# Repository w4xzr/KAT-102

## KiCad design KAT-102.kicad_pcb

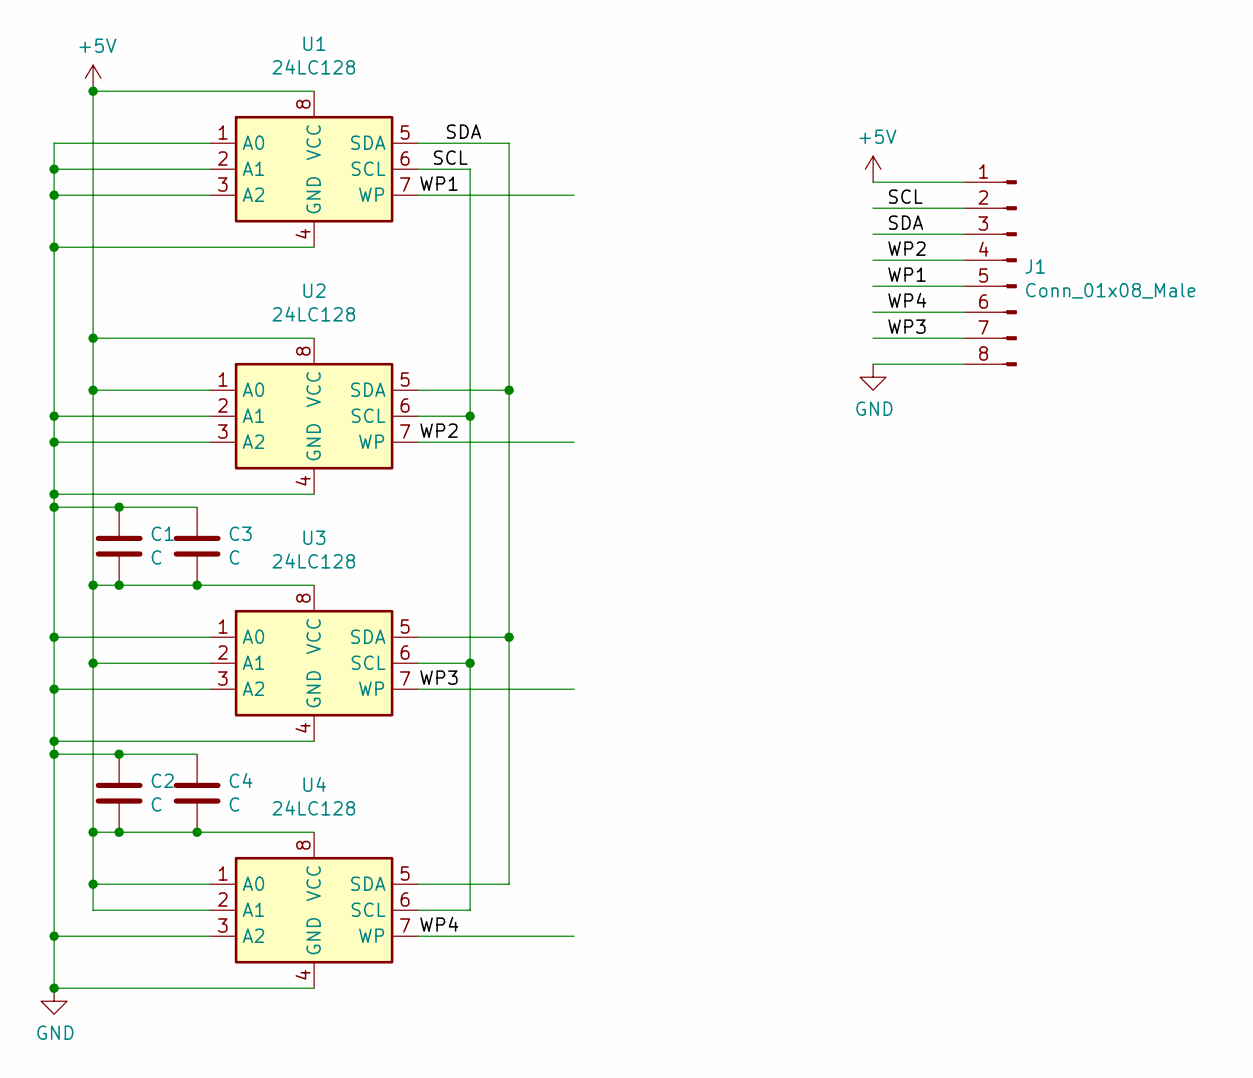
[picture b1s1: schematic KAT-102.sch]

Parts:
C1, C2, C3, C4: C; C_0805_2012Metric
J1: Conn_01x08_Male; PinHeader_1x08_P2.54mm_Vertical
U1, U2, U3, U4: 24LC128; SOIC-8_3.9x4.9mm_P1.27mm

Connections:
+5V: C1.2, C2.2, C3.2, C4.2, J1.1, U1.8 (VCC), U2.1 (A0), U2.8 (VCC), U3.2 (A1), U3.8 (VCC), U4.1 (A0), U4.2 (A1), U4.8 (VCC)
/SCL: J1.2, U1.6 (SCL), U2.6 (SCL), U3.6 (SCL), U4.6 (SCL)
/SDA: J1.3, U1.5 (SDA), U2.5 (SDA), U3.5 (SDA), U4.5 (SDA)
/WP1: J1.5, U1.7 (WP)
/WP2: J1.4, U2.7 (WP)
/WP3: J1.7, U3.7 (WP)
/WP4: J1.6, U4.7 (WP)
GND: C1.1, C2.1, C3.1, C4.1, J1.8, U1.1 (A0), U1.2 (A1), U1.3 (A2), U1.4 (GND), U2.2 (A1), U2.3 (A2), U2.4 (GND), U3.1 (A0), U3.3 (A2), U3.4 (GND), U4.3 (A2), U4.4 (GND)

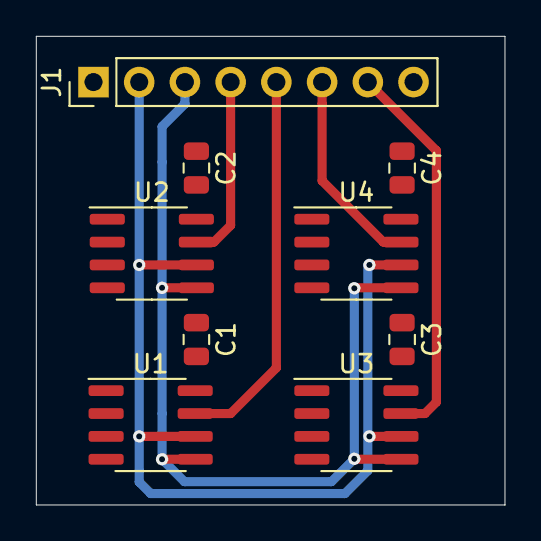
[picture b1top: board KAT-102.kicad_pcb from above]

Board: 2 copper layers, 26.0 x 26.0 mm, 9 parts (0 on the bottom side), 8 nets.

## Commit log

2020-07-03 finit
2020-07-03 modified: .travis.yml
2020-07-03 Updated Images: Fri Jul 3 22:27:42 UTC 2020 (Build 2)
    [skip ci]
2020-07-03 [ImgBot] Optimize images
    *Total -- 147.09kb -> 113.04kb (23.15%)
    /Images/Front.png -- 100.52kb -> 76.15kb (24.24%)
    /Images/Back.png -- 46.58kb -> 36.89kb (20.8%)
2020-07-03 Updated Images: Fri Jul 3 23:51:19 UTC 2020 (Build 7)
    [skip ci]
2020-07-03 Added README.md
2020-07-03 Updated Images: Fri Jul 3 23:59:48 UTC 2020 (Build 12)
    [skip ci]
